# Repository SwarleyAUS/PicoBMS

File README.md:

# PicoBMS
Raspberry Pi Pico-based Battery Management System for 6-24S Lithium battery packs

Devleoped in KiCAD

Functionality:
- 6-24S cell monitoring and balancing through LTC6803-3
- XT30 charge and battery ports
- JST-XH balance jacks (12P & 13P)
- Dual thermister inputs
- Charge current sensing
- Opto-isolated CAN breakout from Pi Pico
- Back to back input MOSFETs for discharge protection

*** THIS DESIGN IS THEORETICALLY COMPLETE BUT UNTESTED ***

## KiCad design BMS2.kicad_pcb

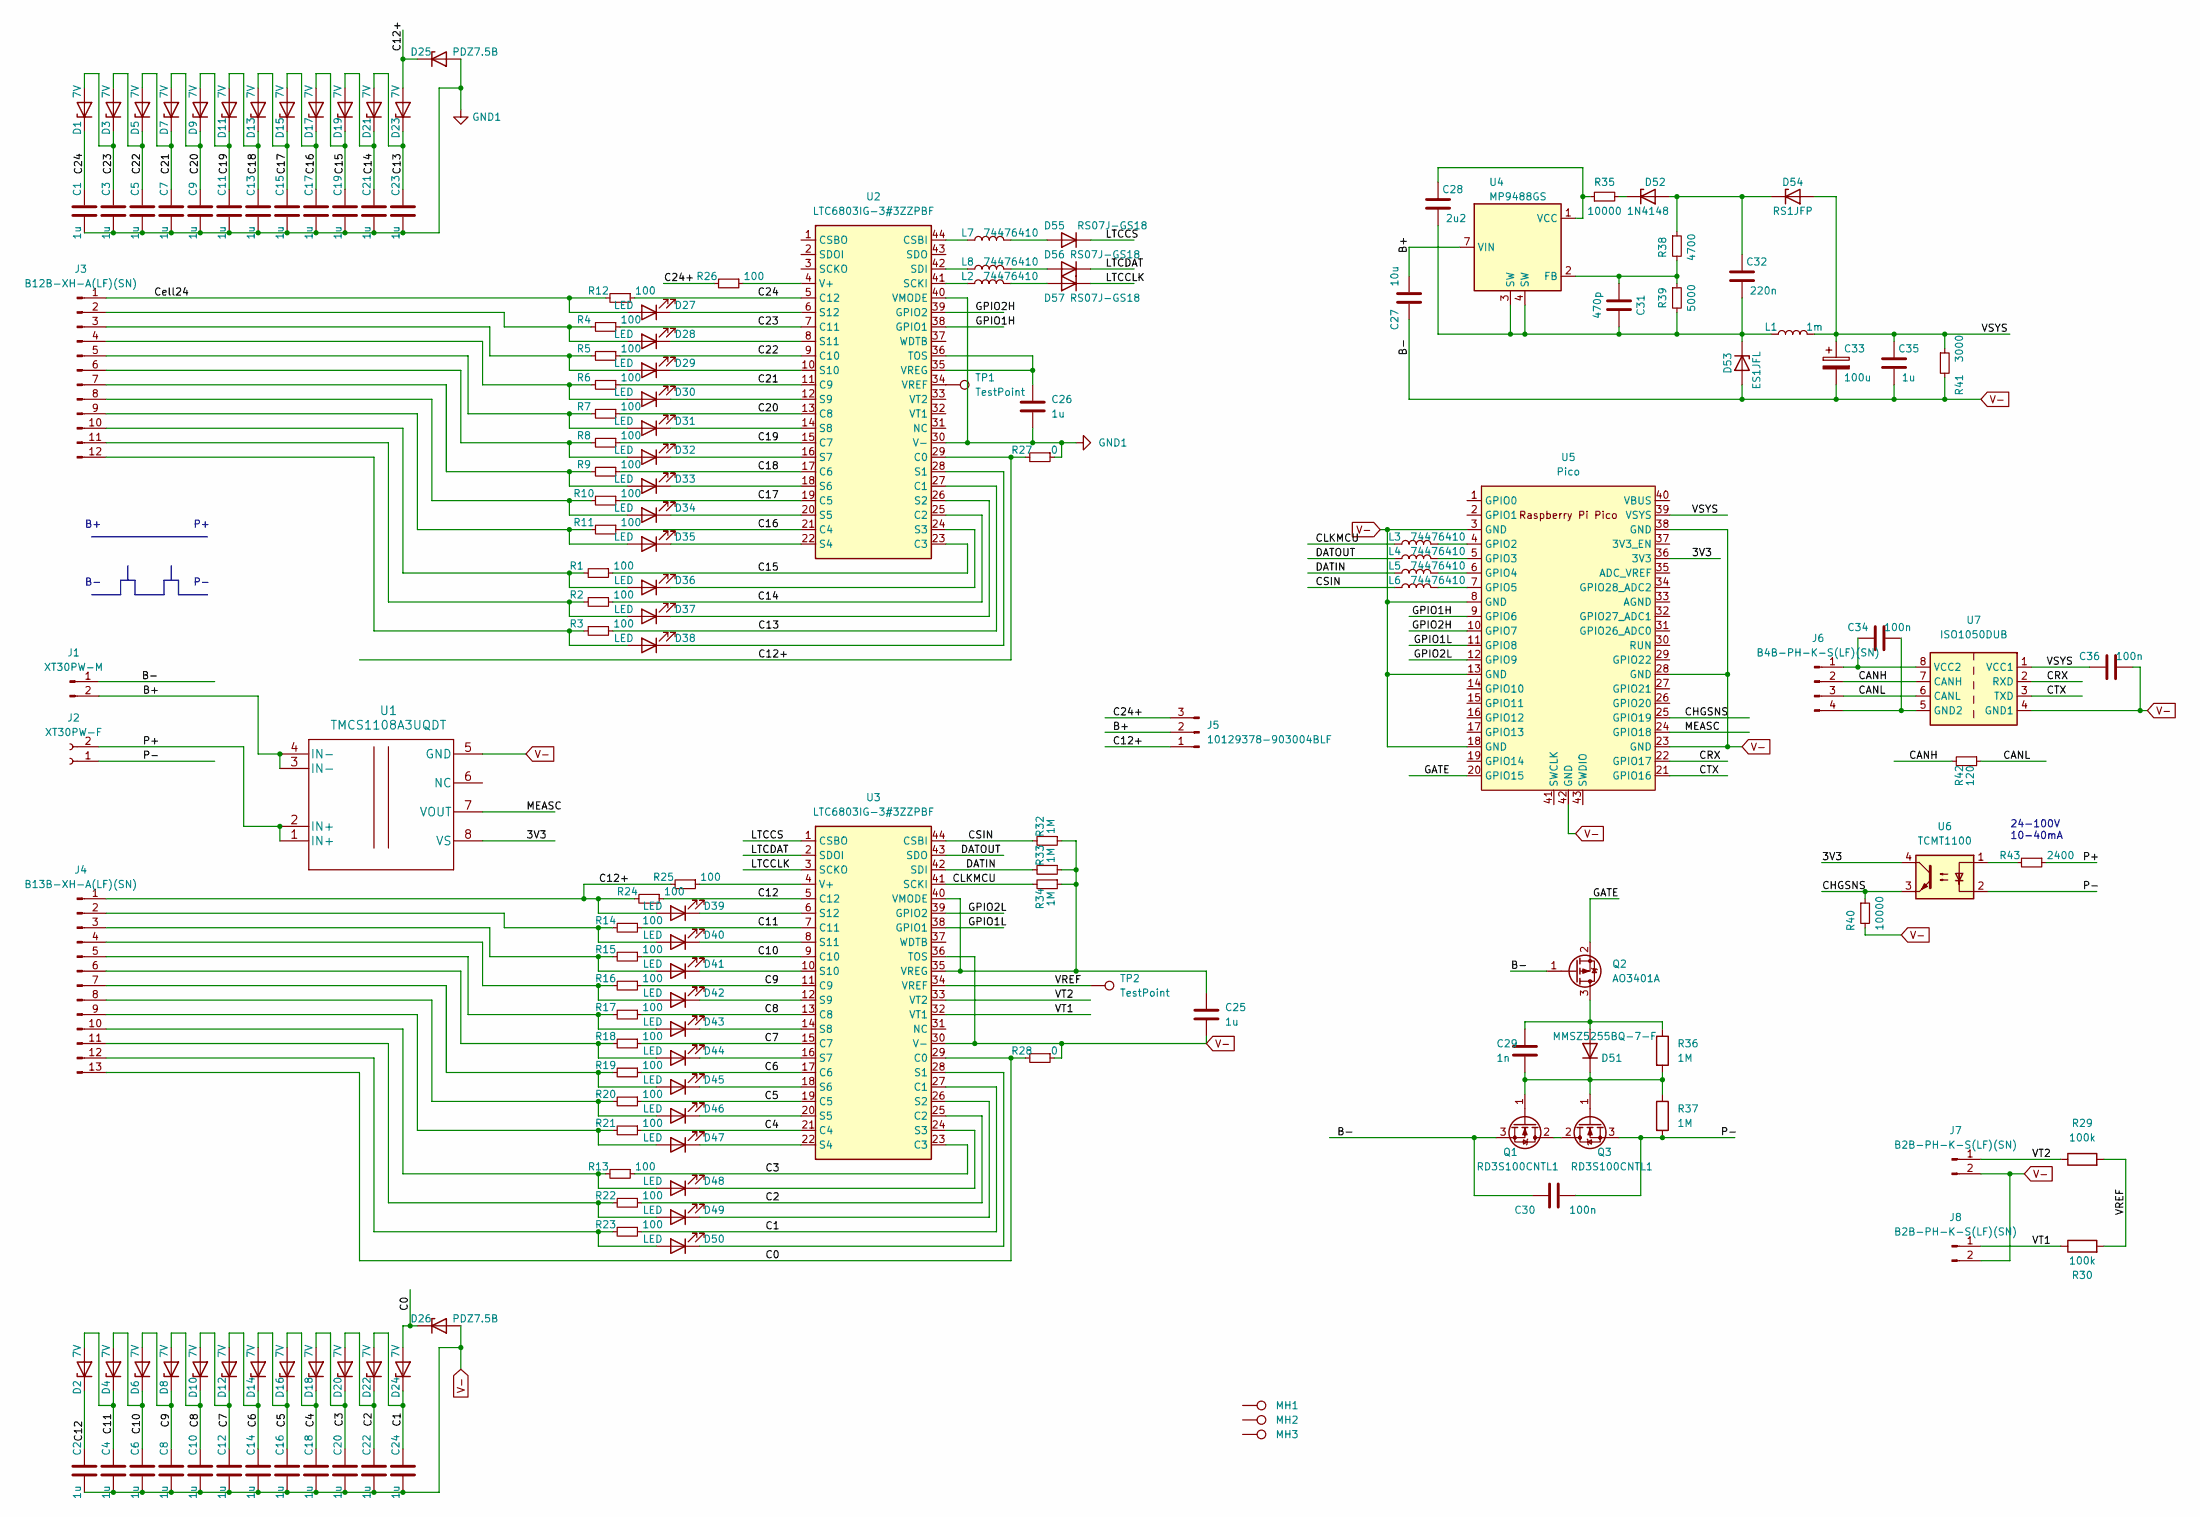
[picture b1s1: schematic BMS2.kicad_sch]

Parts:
C1, C2, C3, C4, C5, C6, C7, C8, C9, C10, C11, C12, C13, C14, C15, C16, C17, C18, C19, C20, C21, C22, C23, C24, C25, C26, C35: 1u; C_0603_1608Metric
C27: 10u; C_1210_3225Metric
C28: 2u2; C_0603_1608Metric
C29: 1n; C_0603_1608Metric
C30, C34, C36: 100n; C_0603_1608Metric
C31: 470p; C_0603_1608Metric
C32: 220n; C_0603_1608Metric
C33: 100u; CP_Elec_5x5.4
D1, D2, D3, D4, D5, D6, D7, D8, D9, D10, D11, D12, D13, D14, D15, D16, D17, D18, D19, D20, D21, D22, D23, D24: 7V; D_SOD-323
D25, D26: PDZ7.5B; D_SOD-323
D27, D28, D29, D30, D31, D32, D33, D34, D35, D36, D37, D38, D39, D40, D41, D42, D43, D44, D45, D46, D47, D48, D49, D50: LED; LED_0603_1608Metric
D51: MMSZ5255BQ-7-F; D_SOD-123
D52: 1N4148; D_SOD-323
D53: ES1JFL; D_SOD-123
D54: RS1JFP; D_SOD-123
D55, D56, D57: RS07J-GS18; D_SMF
J1: XT30PW-M; AMASS_XT30PW-M_1x02_P2.50mm_Horizontal
J2: XT30PW-F; AMASS_XT30PW-F_1x02_P2.50mm_Horizontal
J3: B12B-XH-A(LF)(SN); JST_XH_B12B-XH-A_1x12_P2.50mm_Vertical
J4: B13B-XH-A(LF)(SN); JST_XH_B13B-XH-A_1x13_P2.50mm_Vertical
J5: 10129378-903004BLF; PinHeader_1x03_P2.54mm_Vertical
J6: B4B-PH-K-S(LF)(SN); JST_PH_B4B-PH-K_1x04_P2.00mm_Vertical
J7, J8: B2B-PH-K-S(LF)(SN); JST_PH_B2B-PH-K_1x02_P2.00mm_Vertical
L1: 1m; L_1812_4532Metric
L2, L3, L4, L5, L6, L7, L8: 74476410; L_0805_2012Metric
MH1, MH2, MH3: TestPoint; MountingHole_3.2mm_M3
Q1, Q3: RD3S100CNTL1; TO-252-2
Q2: AO3401A; SOT-23
R1, R2, R3, R4, R5, R6, R7, R8, R9, R10, R11, R12, R13, R14, R15, R16, R17, R18, R19, R20, R21, R22, R23, R24, R25, R26: 100; R_0603_1608Metric
R27, R28: 0; R_0603_1608Metric
R29, R30: 100k; R_0603_1608Metric
R32, R33, R34, R36, R37: 1M; R_0603_1608Metric
R35, R40: 10000; R_0603_1608Metric
R38: 4700; R_0603_1608Metric
R39: 5000; R_0603_1608Metric
R41: 3000; R_0603_1608Metric
R42: 120; R_0603_1608Metric
R43: 2400; R_0603_1608Metric
TP1, TP2: TestPoint; TestPoint_THTPad_D1.5mm_Drill0.7mm
U1: TMCS1108A3UQDT; SOIC-8_3.9x4.9mm_P1.27mm
U2, U3: LTC6803IG-3#3ZZPBF; SSOP-44_5.3x12.8mm_P0.5mm
U4: MP9488GS; SOIC-8_3.9x4.9mm_P1.27mm
U5: Pico; RPi_Pico_SMD_TH
U6: TCMT1100; SOP-4_4.4x2.6mm_P1.27mm
U7: ISO1050DUB; SOP-8_6.62x9.15mm_P2.54mm

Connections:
/3V3: U1.8 (VS), U5.36 (3V3), U6.4
/B+: C27.2, J1.2, J5.2, U1.3 (IN-), U1.4 (IN-), U4.7 (VIN)
/C0: D24.2 (A), D26.1 (K), J4.13, R28.2, U3.29 (C0)
/C1: C24.1, D22.2 (A), D24.1 (K), R23.1, U3.27 (C1)
/C2: C22.1, D20.2 (A), D22.1 (K), R22.1, U3.25 (C2)
/C3: C20.1, D18.2 (A), D20.1 (K), R13.1, U3.23 (C3)
/C4: C18.1, D16.2 (A), D18.1 (K), R21.1, U3.21 (C4)
/C5: C16.1, D14.2 (A), D16.1 (K), R20.1, U3.19 (C5)
/C6: C14.1, D12.2 (A), D14.1 (K), R19.1, U3.17 (C6)
/C7: C12.1, D10.2 (A), D12.1 (K), R18.1, U3.15 (C7)
/C8: C10.1, D8.2 (A), D10.1 (K), R17.1, U3.13 (C8)
/C9: C8.1, D6.2 (A), D8.1 (K), R16.1, U3.11 (C9)
/C10: C6.1, D4.2 (A), D6.1 (K), R15.1, U3.9 (C10)
/C11: C4.1, D2.2 (A), D4.1 (K), R14.1, U3.7 (C11)
/C12: C2.1, D2.1 (K), R24.1, U3.5 (C12)
/C12+: D23.2 (A), D25.1 (K), D39.2 (A), J4.1, J5.1, R24.2, R25.2, R27.2, U2.29 (C0)
/C13: C23.1, D21.2 (A), D23.1 (K), R3.1, U2.27 (C1)
/C14: C21.1, D19.2 (A), D21.1 (K), R2.1, U2.25 (C2)
/C15: C19.1, D17.2 (A), D19.1 (K), R1.1, U2.23 (C3)
/C16: C17.1, D15.2 (A), D17.1 (K), R11.1, U2.21 (C4)
/C17: C15.1, D13.2 (A), D15.1 (K), R10.1, U2.19 (C5)
/C18: C13.1, D11.2 (A), D13.1 (K), R9.1, U2.17 (C6)
/C19: C11.1, D9.2 (A), D11.1 (K), R8.1, U2.15 (C7)
/C20: C9.1, D7.2 (A), D9.1 (K), R7.1, U2.13 (C8)
/C21: C7.1, D5.2 (A), D7.1 (K), R6.1, U2.11 (C9)
/C22: C5.1, D3.2 (A), D5.1 (K), R5.1, U2.9 (C10)
/C23: C3.1, D1.2 (A), D3.1 (K), R4.1, U2.7 (C11)
/C24: C1.1, D1.1 (K), R12.1, U2.5 (C12)
/C24+: J5.3, R26.2
/CANH: J6.2, R42.2, U7.7 (CANH)
/CANL: J6.3, R42.1, U7.6 (CANL)
/CHGSNS: R40.1, U5.25 (GPIO19), U6.3
/CLKMCU: L3.1, R34.2, U3.41 (SCKI)
/CRX: U5.22 (GPIO17), U7.2 (RXD)
/CSIN: L6.1, R32.2, U3.44 (CSBI)
/CTX: U5.21 (GPIO16), U7.3 (TXD)
/Cell24: D27.2 (A), J3.1, R12.2
/DATIN: L5.1, R33.2, U3.42 (SDI)
/DATOUT: L4.1, U3.43 (SDO)
/GATE: Q2.2 (S), U5.20 (GPIO15)
/GPIO1H: U2.38 (GPIO1), U5.9 (GPIO6)
/GPIO1L: U3.38 (GPIO1), U5.11 (GPIO8)
/GPIO2H: U2.39 (GPIO2), U5.10 (GPIO7)
/GPIO2L: U3.39 (GPIO2), U5.12 (GPIO9)
/LTCCLK: D57.1 (K), U3.3 (SCKO)
/LTCCS: D55.1 (K), U3.1 (CSBO)
/LTCDAT: D56.1 (K), U3.2 (SDOI)
/MEASC: U1.7 (VOUT), U5.24 (GPIO18)
/P+: J2.2, R43.1, U1.1 (IN+), U1.2 (IN+)
/P-: C30.2, J2.1, Q3.3 (S), R37.2, U6.2
/VREF: R29.2, R30.2, TP2.1, U3.34 (VREF)
/VSYS: C33.1, C35.1, C36.1, D54.2 (A), L1.2, R41.1, U5.39 (VSYS), U7.1 (VCC1)
/VT1: J8.1, R30.1, U3.32 (VT1)
/VT2: J7.1, R29.1, U3.33 (VT2)
GND1: C1.2, C3.2, C5.2, C7.2, C9.2, C11.2, C13.2, C15.2, C17.2, C19.2, C21.2, C23.2, C26.2, D25.2 (A), R27.1, U2.30 (V-), U2.40 (VMODE)
unnamed: C25.1, R32.1, R33.1, R34.1, U3.35 (VREG), U3.40 (VMODE)
unnamed: C26.1, U2.35 (VREG), U2.36 (TOS)
unnamed: C28.1, R35.1, U4.1 (VCC)
unnamed: C28.2, C31.1, C32.2, D53.1 (K), L1.1, R39.2, U4.3 (SW), U4.4 (SW)
unnamed: C29.1, D51.2 (K), Q1.1 (G), Q3.1 (G), R36.2, R37.1
unnamed: C29.2, D51.1 (A), Q2.3 (D), R36.1
unnamed: C31.2, R38.2, R39.1, U4.2 (FB)
unnamed: C32.1, D52.2 (A), D54.1 (K), R38.1
unnamed: C34.1, J6.1, U7.8 (VCC2)
unnamed: C34.2, J6.4, U7.5 (GND2)
unnamed: D27.1 (K), U2.6 (S12)
unnamed: D28.1 (K), U2.8 (S11)
unnamed: D28.2 (A), J3.2, R4.2
unnamed: D29.1 (K), U2.10 (S10)
unnamed: D29.2 (A), J3.3, R5.2
unnamed: D30.1 (K), U2.12 (S9)
unnamed: D30.2 (A), J3.4, R6.2
unnamed: D31.1 (K), U2.14 (S8)
unnamed: D31.2 (A), J3.5, R7.2
unnamed: D32.1 (K), U2.16 (S7)
unnamed: D32.2 (A), J3.6, R8.2
unnamed: D33.1 (K), U2.18 (S6)
unnamed: D33.2 (A), J3.7, R9.2
unnamed: D34.1 (K), U2.20 (S5)
unnamed: D34.2 (A), J3.8, R10.2
unnamed: D35.1 (K), U2.22 (S4)
unnamed: D35.2 (A), J3.9, R11.2
unnamed: D36.1 (K), U2.24 (S3)
unnamed: D36.2 (A), J3.10, R1.2
unnamed: D37.1 (K), U2.26 (S2)
unnamed: D37.2 (A), J3.11, R2.2
unnamed: D38.1 (K), U2.28 (S1)
unnamed: D38.2 (A), J3.12, R3.2
unnamed: D39.1 (K), U3.6 (S12)
unnamed: D40.1 (K), U3.8 (S11)
unnamed: D40.2 (A), J4.2, R14.2
unnamed: D41.1 (K), U3.10 (S10)
unnamed: D41.2 (A), J4.3, R15.2
unnamed: D42.1 (K), U3.12 (S9)
unnamed: D42.2 (A), J4.4, R16.2
unnamed: D43.1 (K), U3.14 (S8)
unnamed: D43.2 (A), J4.5, R17.2
unnamed: D44.1 (K), U3.16 (S7)
unnamed: D44.2 (A), J4.6, R18.2
unnamed: D45.1 (K), U3.18 (S6)
unnamed: D45.2 (A), J4.7, R19.2
unnamed: D46.1 (K), U3.20 (S5)
unnamed: D46.2 (A), J4.8, R20.2
unnamed: D47.1 (K), U3.22 (S4)
unnamed: D47.2 (A), J4.9, R21.2
unnamed: D48.1 (K), U3.24 (S3)
unnamed: D48.2 (A), J4.10, R13.2
unnamed: D49.1 (K), U3.26 (S2)
unnamed: D49.2 (A), J4.11, R22.2
unnamed: D50.1 (K), U3.28 (S1)
unnamed: D50.2 (A), J4.12, R23.2
unnamed: D52.1 (K), R35.2
unnamed: D55.2 (A), L7.2
unnamed: D56.2 (A), L8.2
unnamed: D57.2 (A), L2.2
unnamed: L2.1, U2.41 (SCKI)
unnamed: L3.2, U5.4 (GPIO2)
unnamed: L4.2, U5.5 (GPIO3)
unnamed: L5.2, U5.6 (GPIO4)
unnamed: L6.2, U5.7 (GPIO5)
unnamed: L7.1, U2.44 (CSBI)
unnamed: L8.1, U2.42 (SDI)
unnamed: Q1.2 (D), Q3.2 (D)
unnamed: R25.1, U3.4 (V+)
unnamed: R26.1, U2.4 (V+)
unnamed: R43.2, U6.1
unnamed: TP1.1, U2.34 (VREF)
V-: C2.2, C4.2, C6.2, C8.2, C10.2, C12.2, C14.2, C16.2, C18.2, C20.2, C22.2, C24.2, C25.2, C27.1, C30.1, C33.2, C35.2, C36.2, D26.2 (A), D53.2 (A), J1.1, J7.2, J8.2, Q1.3 (S), Q2.1 (G), R28.1, R40.2, R41.2, U1.5 (GND), U3.30 (V-), U3.36 (TOS), U5.3 (GND), U5.8 (GND), U5.13 (GND), U5.18 (GND), U5.23 (GND), U5.28 (GND), U5.38 (GND), U5.42 (GND), U7.4 (GND1)

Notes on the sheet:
24-100V 10-40mA

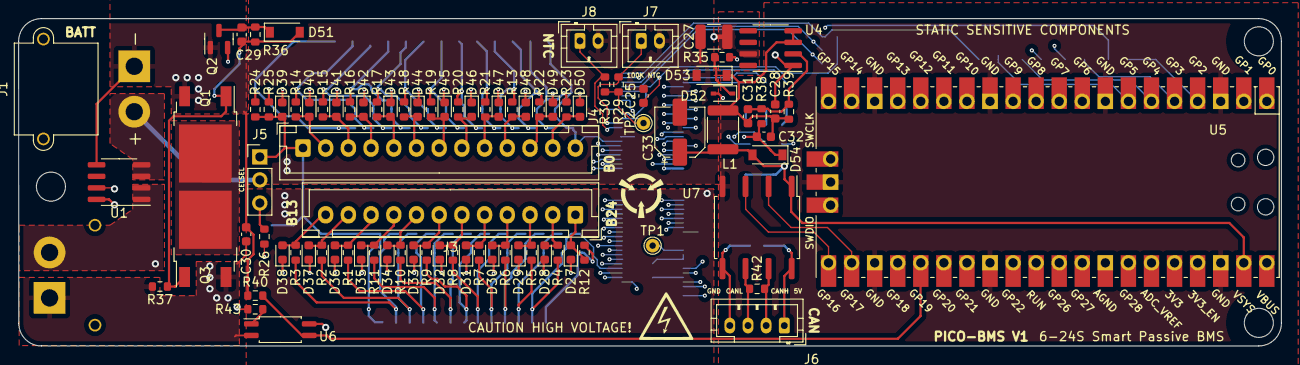
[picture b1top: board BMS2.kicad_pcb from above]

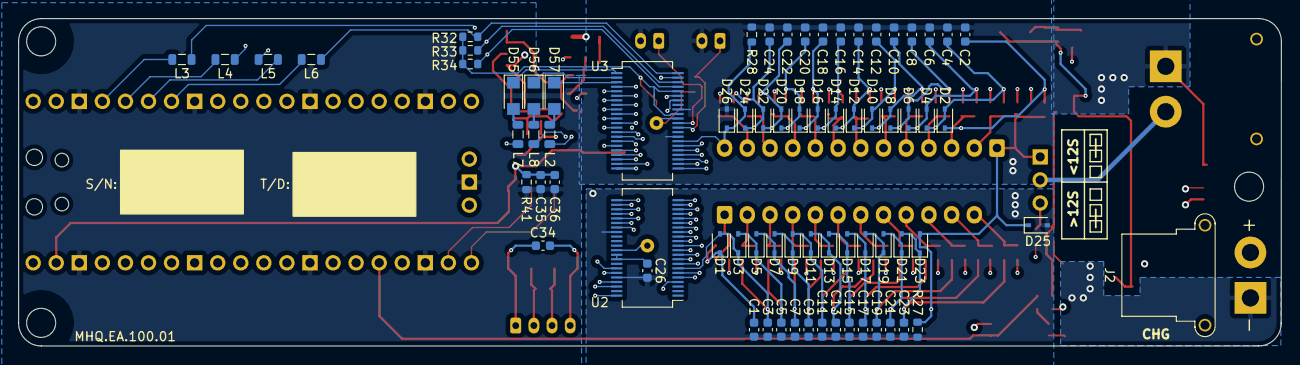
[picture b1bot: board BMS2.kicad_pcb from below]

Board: 4 copper layers, 139.0 x 36.0 mm, 166 parts (73 on the bottom side), 128 nets.

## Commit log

2023-05-29 KiCAD files
